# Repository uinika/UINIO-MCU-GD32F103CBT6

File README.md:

# UINIO-MCU-GD32F103CBT6 核心板

[**UINIO-MCU-GD32F103CBT6**](https://gitee.com/uinika/UINIO-MCU-GD32F103CBT6) 是一款基于 [**兆易创新**](https://www.gigadevice.com.cn/) 国产 **LQFP48** 封装的 **GD32F103Cxxx** 系列微控制器（`GD32F103CBT6`、`GD32F103C8T6`、`GD32F103C6T6`、`GD32F103C4T6`）的核心板电路设计，该微控制器基于 **ARM Cortex-M3** 内核架构，主频可以达到 `108MHz`，片上载有 `16K ~ 128K` 容量的 Flash 存储器，以及 `6K ~ 20K` 的 SRAM 存储器，并且拥有 2 到 3 组 `USART`、`I2C`、`SPI`，以及 1 到 2 组 `I2S`、`12 位 ADC`、`12 位 DAC`，同时支持 **USB 2.0 FS OTG** 协议，整体上属于外设资源比较完善的高性价比主控芯片产品。

## 设计概要

1. 引出了 **GD32F103Cxxx** 系列微控制器上面的全部 GPIO 引脚资源；
2. `VSSA` 模拟地引脚使用了 `1KΩ 100Mhz` 的**磁珠**进行单点接地；
3. 单独提供有 4 线制 **SWD** 下载接口，便于快速与 [UINIO-DAP-Link](http://uinio.com/Project/UINIO-DAP-Link) 建立连接；
4. 使用 `8MHz` 与 `32.768KHz` 两枚贴片晶振，并且分别进行了简单的**包地**处理；
5. 主控芯片的 **USB 2.0 FS OTG** 被连接至 USB Type-C 接口，并且加入 `1.5 KΩ` 上拉电阻兼容 **USB-PD** 快充协议；

## 参考技术文档

[UinIO.com 电子技术实验室](http://uinio.com/) 为 UINIO-MCU-GD32F103CBT6 开源项目提供了如下一系列技术参考资料：

1. [《兆易创新 UINIO-MCU-GD32 标准库开发指南》](http://uinio.com/Project/UINIO-MCU-GD32/)
2. [《ARM 调试工具 UINIO-DAP-Link 应用详解》](http://uinio.com/Project/UINIO-DAP-Link/)
3. [《BOM 交互式物料清单与 PCB 布线在线预览》](http://uinio.com/archives/BOM/UINIO-MCU-GD32F103CBT6.html)

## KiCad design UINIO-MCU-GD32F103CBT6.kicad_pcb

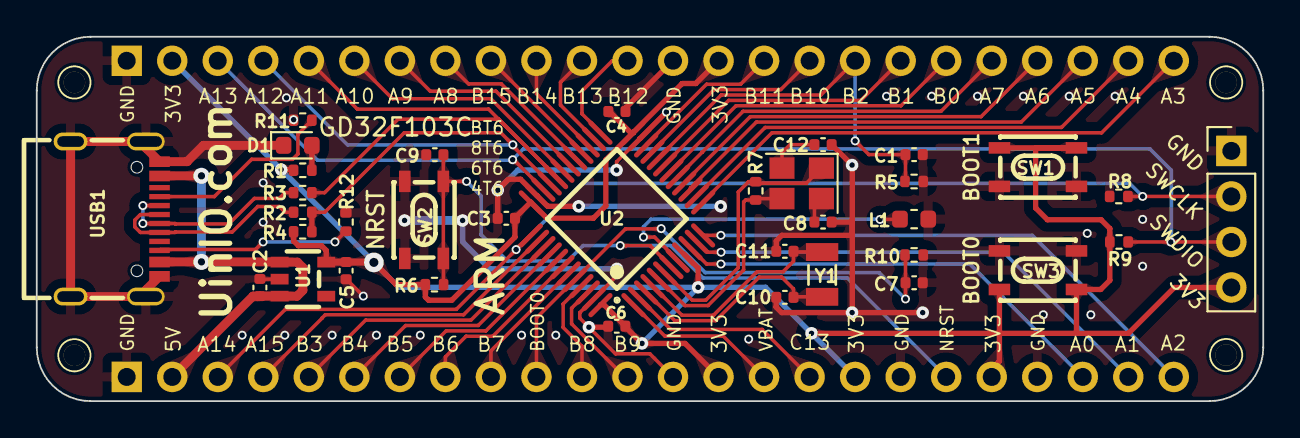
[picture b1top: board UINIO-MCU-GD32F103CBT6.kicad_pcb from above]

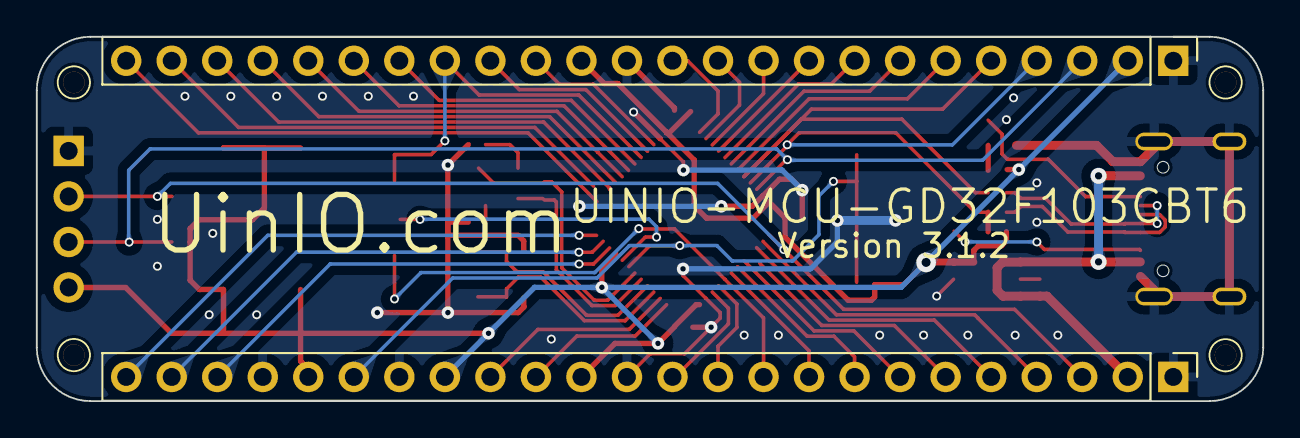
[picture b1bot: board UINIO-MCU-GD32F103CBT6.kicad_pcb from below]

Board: 2 copper layers, 68.4 x 20.3 mm, 41 parts (2 on the bottom side), 51 nets.

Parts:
C1, C3, C4, C6, C7, C9: 0.1uF; C_0402_1005Metric
C2, C5: 1uF; C_0402_1005Metric
C8, C12: 20pF; C_0402_1005Metric
C10, C11: 10pF; C_0402_1005Metric
D1: LED_Red; LED_0603_1608Metric
HOLE**: Hole-1mm
HOLE**#2, HOLE**#3, HOLE**#4: Hole-1mm
J1, J2: Conn_01x24_Pin; PinHeader_1x24_P2.54mm_Vertical
J3: Conn_01x04_Pin; PinHeader_1x04_P2.54mm_Vertical
L1: 1KΩ 100Mhz; L_0603_1608Metric
R1: 2K; R_0402_1005Metric
R2, R3: 50R; R_0402_1005Metric
R4: 1.5K; R_0402_1005Metric
R5, R6, R8, R9, R10: 10K; R_0402_1005Metric
R7: 1M; R_0402_1005Metric
R11, R12: 5.1K; R_0402_1005Metric
SW1: BOOT1; KEY-SMD_4P-L4.2-W3.4-P2.15-LS4.7
SW2: NRST; KEY-SMD_4P-L4.2-W3.4-P2.15-LS4.7
SW3: BOOT0; KEY-SMD_4P-L4.2-W3.4-P2.15-LS4.7
U1: ME6211C33M5G-N; SOT-23-5_L3.0-W1.7-P0.95-LS2.8-BR
U2: GD32F103C8T6; TQFP-48_L7.0-W7.0-P0.50-LS9.0-BL
USB1: USB_Type_C_16Pin; USB-C-SMD_TYPEC-304J-BCP16
Y1: 32.768KHz; CRYSTAL-FC135-32.768
Y2: 8MHz; Crystal_SMD_3225-4Pin_3.2x2.5mm

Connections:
/BOOT0: C7.2, J2.10, R10.1, U2.44 (BOOT0)
/NRST: C9.1, J2.19, R6.2, SW2.1, SW2.2, U2.7 (NRST)
/PA0: J2.22, U2.10 (PA0_WAKEUP)
/PA1: J2.23, U2.11 (PA1)
/PA2: J2.24, U2.12 (PA2)
/PA3: J1.24, U2.13 (PA3)
/PA4: J1.23, U2.14 (PA4)
/PA5: J1.22, U2.15 (PA5)
/PA6: J1.21, U2.16 (PA6)
/PA7: J1.20, U2.17 (PA7)
/PA8: J1.8, U2.29 (PA8)
/PA9: J1.7, U2.30 (PA9)
/PA10: J1.6, U2.31 (PA10)
/PA11: J1.5, R3.1, U2.32 (PA11)
/PA12: J1.4, R2.1, R4.2, U2.33 (PA12)
/PA13/SWDIO: J1.3, J3.3, R9.1, U2.34 (PA13)
/PA14/SWCLK: J2.3, J3.2, R8.2, U2.37 (PA14)
/PA15: J2.4, U2.38 (PA15)
/PB0: J1.19, U2.18 (PB0)
/PB1: J1.18, U2.19 (PB1)
/PB2/BOOT1: C1.2, J1.17, R5.1, U2.20 (PB2)
/PB3: J2.5, U2.39 (PB3)
/PB4: J2.6, U2.40 (PB4)
/PB5: J2.7, U2.41 (PB5)
/PB6: J2.8, U2.42 (PB6)
/PB7: J2.9, U2.43 (PB7)
/PB8: J2.11, U2.45 (PB8)
/PB9: J2.12, U2.46 (PB9)
/PB10: J1.16, U2.21 (PB10)
/PB11: J1.15, U2.22 (PB11)
/PB12: J1.12, U2.25 (PB12)
/PB13: J1.11, U2.26 (PB13)
/PB14: J1.10, U2.27 (PB14)
/PB15: J1.9, U2.28 (PB15)
/PC13: J2.16, U2.2 (PC13_TAMPER_RTC)
/USB_Data+: R2.2, USB1.A6 (DP1), USB1.B6 (DP2)
/USB_Data-: R3.2, USB1.A7 (DN1), USB1.B7 (DN2)
/VBAT: J2.15, U2.1 (VBAT)
/VDD_3.3V: C3.2, C4.2, C5.2, C6.2, J1.2, J1.14, J2.14, J2.17, J2.20, J3.4, R1.2, R4.1, R6.1, R9.2, SW1.3, SW1.4, SW3.3, SW3.4, U1.5 (Vout), U2.9 (VDDA), U2.24 (VDD_1), U2.36 (VDD_2), U2.48 (VDD_3)
/VDD_5V: C2.2, J2.2, U1.1 (Vin), U1.3 (CE), USB1.A4B9 (VBUS), USB1.B4A9 (VBUS)
GND: C1.1, C2.1, C3.1, C4.1, C5.1, C6.1, C7.1, C8.1, C9.2, C10.1, C11.1, C12.1, D1.1 (K), J1.1, J1.13, J2.1, J2.13, J2.18, J2.21, J3.1, L1.1, R5.2, R8.1, R10.2, R11.2, R12.2, SW1.1, SW1.2, SW2.3, SW2.4, SW3.1, SW3.2, U1.2 (Vss), U2.23 (VSS_1), U2.35 (VSS_2), U2.47 (VSS_3), USB1.13 (GND), USB1.14 (GND), USB1.15 (GND), USB1.16 (GND), USB1.A1B12 (GND), USB1.B1A12 (GND)
unnamed: C8.2, Y2.4
unnamed: C12.2, Y2.2
unnamed: D1.2 (A), R1.1
unnamed: C10.2, U2.3 (PC14_OSC32_IN), Y1.2 (GND)
unnamed: C11.2, U2.4 (PC15_OSC32_OUT), Y1.1
unnamed: R7.1, U2.5 (PD0_OSC_IN), Y2.3
unnamed: R7.2, U2.6 (PD1_OSC_OUT), Y2.1
unnamed: L1.2, U2.8 (VSSA)
unnamed: R11.1, USB1.A5 (CC1)
unnamed: R12.1, USB1.B5 (CC2)

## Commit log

2023-01-28 Initialization project.
2023-01-29 Drawing schematic diagram.
2023-01-29 Complete schematic drawing.
2023-01-30 Finish PCB Layout.
2023-01-30 Finish UINIO-MCU-GD32F103C version 1.0.0.
2023-01-31 Release UINIO-MCU-GD32F103C version 1.0.0.
2023-06-28 Prepare version 2.0.0.
2023-06-28 Release UINIO-MCU-GD32F103C version 2.0.0.
2023-07-06 Update PCB.
2023-07-11 Update README.md.
2023-08-30 Release UINIO-MCU-GD32F103C version 3.0.0.
2023-12-27 Release UINIO-MCU-GD32F103CBT6 version 3.1.0.
2024-01-11 Release UINIO-MCU-GD32F103CBT6 version 3.1.1.
2024-01-31 Release UINIO-MCU-GD32F103CBT6 version 3.1.2.
